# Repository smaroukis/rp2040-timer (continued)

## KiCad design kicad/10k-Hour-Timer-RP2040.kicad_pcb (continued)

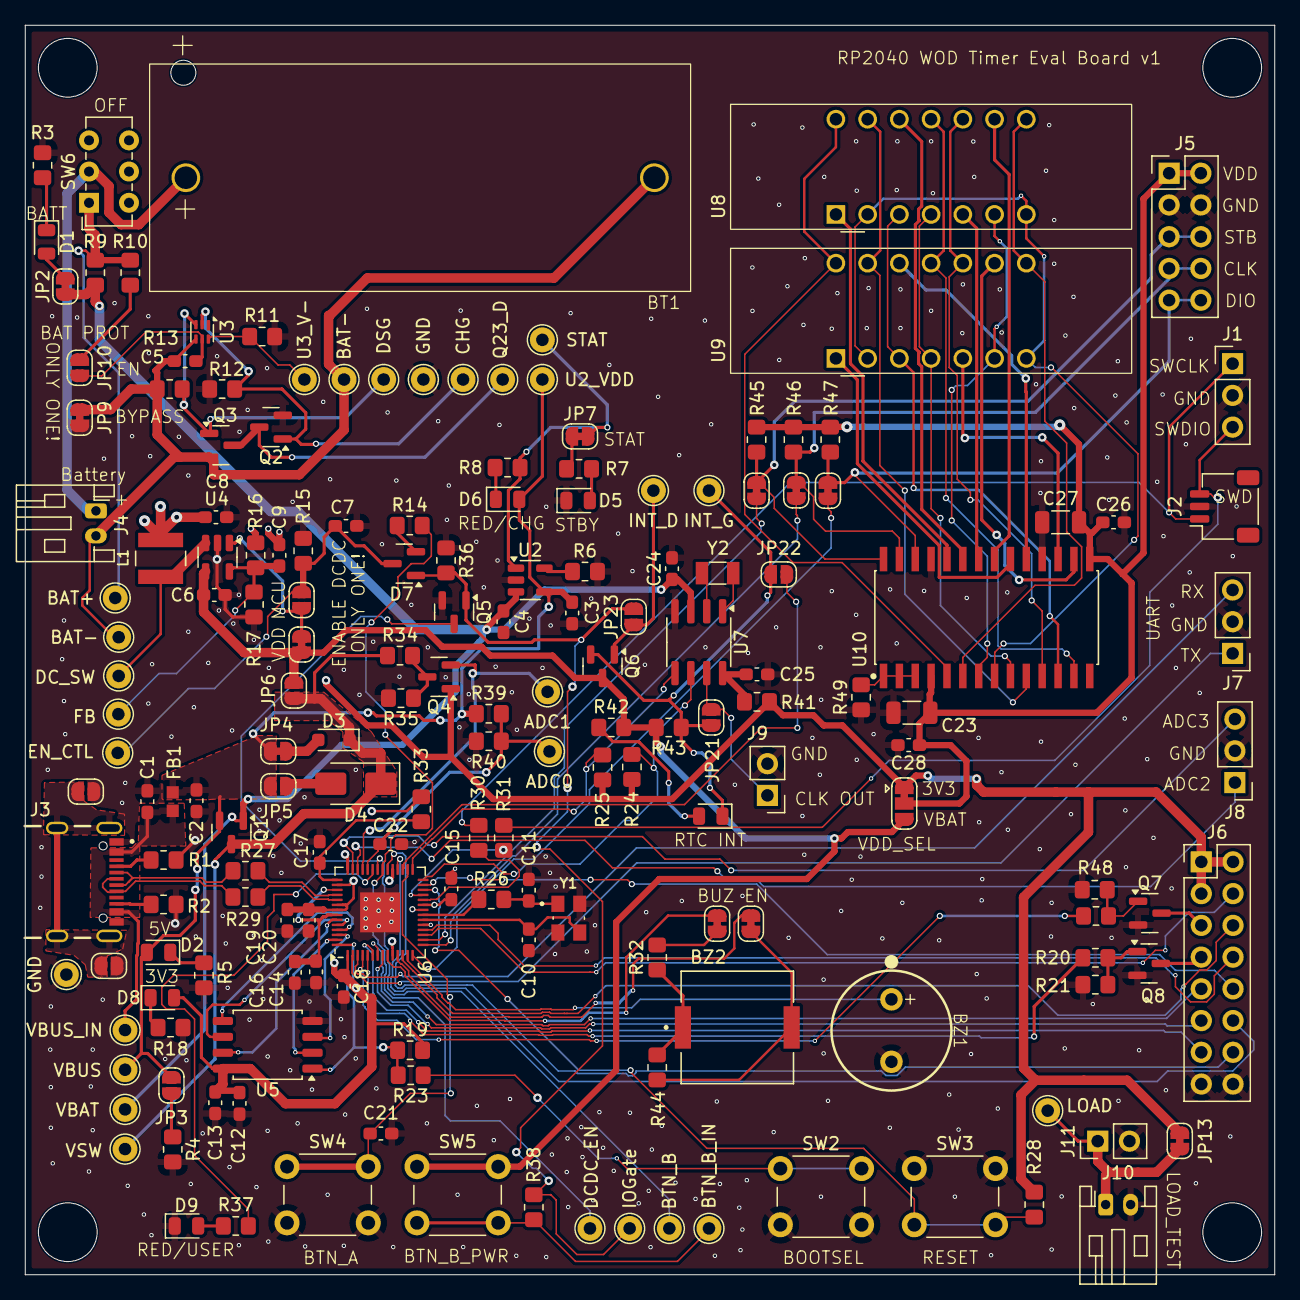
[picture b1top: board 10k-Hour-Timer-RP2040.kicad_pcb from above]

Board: 4 copper layers, 100.0 x 100.0 mm, 180 parts (0 on the bottom side), 128 nets.

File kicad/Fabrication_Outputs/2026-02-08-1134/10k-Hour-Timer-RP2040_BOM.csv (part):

"Subsystem","Reference","Lab_In_Stock","Value","DNP","Exclude from BOM","Exclude from Board","Footprint","Description","Manufacturer","MPN","Supplier 1","Supplier 1 URL","Supplier 1 SKU","Package","Supplier 2 URL","Supplier 2","Supplier 2 SKU"
"","BOM1","","JST PH 2.0mm Connector Kit","DNP","Excluded from BOM","Excluded from board","","For Board Auxiliary order items - connectors, batteries, etc","","","Digikey","https://www.digikey.jp/en/products/detail/adafruit-industrie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","","","","",""
"","BOM2","","Crimp Pliers for JST-PH connectors","DNP","Excluded from BOM","Excluded from board","","Micro terminal crimper down to 1.0mm barrel width. Works well for JST-PH - use the 1.4mm or 1.6mm barrel size.","Engineer","PA-09","Amazon","https://www.amazon.co.jp/-/en/Engineer-Precision-Crimping-Te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","","","","",""
"","BOM3","","Coin Vibration Motor 3V","DNP","Excluded from BOM","Excluded from board","","9000rpm Flat Vibration Motor 3V Vibration Motors ROHS 6mm","Leader","LCM0720A3134F","LCSC","https://lcsc.com/product-detail/Vibration-Motors_LEADER-LCM0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","C2895081","","","",""
"05-MCU-XTAL-FLASH","SW1","Y","B3U-1100PM","DNP","Excluded from BOM","Excluded from board","Button_Switch_SMD:SW_SPST_B3U-1100P","SWITCH TACTILE SPST-NO 0.05A 12V","omron","B3U-1100PM","Digikey","https://www.digikey.jp/en/products/detail/omron-electronics-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","","SMD 4mmx2.5mm","","",""
"04-Batt-Prot","SW6","THS","SW_SPDT","DNP","","","Button_Switch_THT:SW_E-Switch_EG1271_SPDT","Switch, single pole double throw","E-Switch","EG1271","Digikey","https://www.digikey.com/en/products/detail/e-switch/EG1271/251335","","","","",""
"05-MCU-XTAL-FLASH","SW2","Y","BOOTSEL","DNP","","","Button_Switch_THT:SW_PUSH_6mm","Push button switch, generic, two pins","(Generic)/TE","(Generic)/1825910-6","(Generic)/Digikey","https://www.digikey.jp/en/products/detail/te-connectivity-al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","","","","",""
"05-MCU-XTAL-FLASH","SW3","Y","RESET","DNP","","","Button_Switch_THT:SW_PUSH_6mm","Push button switch, generic, two pins","(Generic)/TE","(Generic)/1825910-6","(Generic)/Digikey","https://www.digikey.jp/en/products/detail/te-connectivity-al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","","","","",""
"06-MCU-IO","SW4","Y","USER_A","DNP","","","Button_Switch_THT:SW_PUSH_6mm","Push button switch, generic, two pins","(Generic)/TE","(Generic)/1825910-6","(Generic)/Digikey","https://www.digikey.jp/en/products/detail/te-connectivity-al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","","PB_6x6","","",""
"06-MCU-IO","SW5","Y","USER_B_PWR","DNP","","","Button_Switch_THT:SW_PUSH_6mm","Push button switch, generic, two pins","(Generic)/TE","(Generic)/1825910-6","(Generic)/Digikey","https://www.digikey.jp/en/products/detail/te-connectivity-al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","","PB_6x6","","",""
"01A-USB","C1","Y","10n","","","","Capacitor_SMD:C_0603_1608Metric_Pad1.08x0.95mm_HandSolder","Unpolarized capacitor","(Generic)","(Generic)","(Generic)","","","0603","","",""
"01A-USB,05-MCU-XTAL-FLASH,06-MCU-IO,07-RTC,08-LED","C2,C13,C15,C16,C18,C19,C21,C22,C24,C26,C28","Y","100n","","","","Capacitor_SMD:C_0603_1608Metric_Pad1.08x0.95mm_HandSolder","Unpolarized capacitor","(Generic)","(Generic)","(Generic)","","","0603","","",""
"02-DCDC,03-Charger,07-RTC","C3,C4,C6,C25","Y","4.7u","","","","Capacitor_SMD:C_0603_1608Metric_Pad1.08x0.95mm_HandSolder","Unpolarized capacitor","(Generic)","(Generic)","(Generic)","https://jlcpcb.com/partdetail/20375-CL10A475KO8NNNC/C19666","C19666","0603","","",""
"04-Batt-Prot","C5","Y","0.1u","","","","Capacitor_SMD:C_0603_1608Metric_Pad1.08x0.95mm_HandSolder","Unpolarized capacitor","(Generic)","(Generic)","(Generic)","","","0603","","",""
"02-DCDC","C7","Y","470n","","","","Capacitor_SMD:C_0603_1608Metric_Pad1.08x0.95mm_HandSolder","","(Generic)","(Generic)","(Generic)","","","0603","","",""
"02-DCDC","C8","","22u","","","","Capacitor_SMD:C_0603_1608Metric_Pad1.08x0.95mm_HandSolder","6.3V 22uF X5R ±20% 0603 Multilayer Ceramic Capacitors MLCC - SMD/SMT ROHS","Samsung Electro-Mechanics","CL10A226MQ8NRNC","LCSC","https://jlcpcb.com/partdetail/60514-CL10A226MQ8NRNC/C59461","C59461","0603","","",""
"02-DCDC","C9","Y","6.8p","","","","Capacitor_SMD:C_0603_1608Metric_Pad1.08x0.95mm_HandSolder","","(Generic)","(Generic)","(Generic)","","","0603","","",""
"05-MCU-XTAL-FLASH","C10,C11","Y","15p","","","","Capacitor_SMD:C_0603_1608Metric_Pad1.08x0.95mm_HandSolder","Unpolarized capacitor","(Generic)","(Generic)","(Generic)","","","0603","","",""
"05-MCU-XTAL-FLASH","C12","Y","2.2u","","","","Capacitor_SMD:C_0603_1608Metric_Pad1.08x0.95mm_HandSolder","Unpolarized capacitor","(Generic)","(Generic)","(Generic)","","","0603","","",""
"05-MCU-XTAL-FLASH","C14,C17,C20","Y","1u","","","","Capacitor_SMD:C_0603_1608Metric_Pad1.08x0.95mm_HandSolder","Unpolarized capacitor","(Generic)","(Generic)","(Generic)","","","0603","","",""
"08-LED","C23,C27","","100u","","","","Capacitor_SMD:C_1206_3216Metric","Unpolarized capacitor","Samsung Electro-Mechanics","CL31A107MQHNNNE","LCSC","https://lcsc.com/product-detail/Multilayer-Ceramic-Capacitor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","C15008","1206","","",""
"02-DCDC,04-Batt-Prot","J4,J10","Y","S2B-PH-K-S_LF__SN_","DNP","","","Connector_JST:JST_PH_S2B-PH-K_1x02_P2.00mm_Horizontal","CONN HEADER R/A 2POS 2MM","JST","S2B-PH-K-S","Digikey","https://www.digikey.jp/en/products/detail/jst-sales-america-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","","NON STANDARD-2 J.S.T.","","",""
"07-RTC","J9,J11","Y","Conn_01x02_Pin","DNP","","","Connector_PinHeader_2.54mm:PinHeader_1x02_P2.54mm_Vertical","Generic connector, single row, 01x02, script generated","","","","","","","","",""
"05-MCU-XTAL-FLASH,06-MCU-IO","J1,J7,J8","Y","Conn_01x03_Pin","DNP","","","Connector_PinHeader_2.54mm:PinHeader_1x03_P2.54mm_Vertical","Generic connector, single row, 01x03, script generated","(Embedded)","(Embedded)","(Embedded)","","","","","",""
"06-MCU-IO","J5","Y","Conn_02x05_Counter_Clockwise","DNP","","","Connector_PinHeader_2.54mm:PinHeader_2x05_P2.54mm_Vertical","Generic connector, double row, 02x05, odd/even pin numbering scheme (row 1 odd numbers, row 2 even numbers), script generated (kicad-library-utils/schlib/autogen/connector/)","","","","","","","","",""
"","J6","Y","Conn_02x08_Counter_Clockwise","DNP","","","Connector_PinHeader_2.54mm:PinHeader_2x08_P2.54mm_Vertical","Generic connector, double row, 02x08, odd/even pin numbering scheme (row 1 odd numbers, row 2 even numbers), script generated (kicad-library-utils/schlib/autogen/connector/)","","","","","","","","",""
"07-RTC","Y2","","ABS07AIG-32.768KHZ-7-T","","","","Crystal:Crystal_SMD_3215-2Pin_3.2x1.5mm","32.768 kHz ±20ppm 水晶振動子 7pF 80 kOhms 2-SMD、リードなし","Abracon LLC","ABS07AIG-32.768KHZ-7-T","Digikey","https://www.digikey.jp/ja/products/detail/abracon-llc/ABS07A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","535-13350-1-ND","2-SMD（3.2x1.5）","","",""
"01A-Power-Mux","D4","","SS14","","","","Diode_SMD:D_SMA","40V 1A Schottky Diode, SMA","onsemi","SS14 (Generic)","Generic","https://lcsc.com/product-detail/Schottky-Diodes_onsemi-SS14_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","C83852","SMA(DO-214AC)","","",""
"01A-Power-Mux","D3","","SOD-323","","","","Diode_SMD:D_SOD-323_HandSoldering","10V 460mV@2A 2A SOD-323 Schottky Diodes ROHS","Nexperia","PMEG1020EA,115","LCSC","https://lcsc.com/product-detail/Schottky-Diodes_Nexperia-PME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","C426863","SOD-323","","",""
"01A-Power-Mux,06-MCU-IO","JP2,JP4,JP7,JP9,JP11,JP13,JP16,JP17,JP18,JP19,JP20","","SolderJumper_2_Bridged","","Excluded from BOM","","Jumper:SolderJumper-2_P1.3mm_Bridged_RoundedPad1.0x1.5mm","Solder Jumper, 2-pole, closed/bridged","","(Embedded)","","","","","","",""
"01A-Power-Mux,01A-USB,07-RTC","JP1,JP3,JP5,JP6,JP10,JP12,JP21,JP22,JP23,JP24","","SolderJumper_2_Open","","Excluded from BOM","","Jumper:SolderJumper-2_P1.3mm_Open_RoundedPad1.0x1.5mm","Solder Jumper, 2-pole, open","","(Embedded)","","","","","","",""
"","JP8","","SolderJumper_3_Bridged12","","Excluded from BOM","","Jumper:SolderJumper-3_P1.3mm_Bridged12_RoundedPad1.0x1.5mm","3-pole Solder Jumper, pins 1+2 closed/bridged","","","","","","","","",""
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
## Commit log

2025-07-06 Initial commit - 10k-Hour-Timer-RP2040 project
    - KiCad schematic and PCB design files
    - Project structure with datasheets and firmware directories
    - README with project overview
2025-07-06 3d model imports
2025-07-07 added charger and power mux
2025-07-08 battery charger and protection
2025-07-09 battery protection and connector
2025-07-09 dc dc start
2025-07-10 test push
2025-07-10 test
2025-07-10 working on dcdc
2025-07-10 dcdc enable and swd
2025-07-13 rp2040 chip start
2025-07-13 mcu periphs
2025-07-14 clock input pins for internal rtc
2025-07-14 added 32.768 oscillator
2025-07-15 low speed xtal added
2025-07-15 external RTC start
2025-07-15 rtc research
2025-07-16 rtc hardware
2025-07-16 rtc additions
2025-07-17 buzzer
2025-07-18 DR ✅ SYS-01-Power-Mux
2025-07-18 DR SYS-02-DCDC ✅
2025-07-18 led indicator silks
2025-07-19 DR SYS-03 Charger ✅
2025-07-19 charger pcb update
2025-07-20 DR SYS-04-Battery Protect ✅
2025-07-20 DR SYS-05-MCU XTAL
2025-07-21 DR SYS-06-MCU-IO ✅
2025-07-22 buzzer edits
2025-07-26 rtc new sheet, pullups
2025-07-27 pre ERC
2025-07-27 ERC done
2025-07-27 floorplanning
2025-07-28 buzzer fp, power mux layout
2025-07-29 layout battery protection
2025-07-29 layout floorplanning
2025-07-30 layout rtc
2025-07-31 resize
2025-07-31 floorplanning batt prot
2025-08-02 layout - 7seg display
2025-08-02 layout - footprints update - may have corrupted kicad_sch project lib
2025-08-02 floorplanning - fixed 7seg symbol issue
2025-08-04 start routing diff pairs
2025-08-04 changed usb port, prepare first bom export
2025-08-05 routing - power
2025-08-11 routing - 3v3 net
2025-08-13 routing - adc
2025-08-16 routing - GPIOs
2025-08-17 DRC to zero errors - still need to check FPs
2025-08-17 prep for FP changes
2025-08-17 updated FPs, ready for final DR before fab
2025-08-31 unknown changes
2026-02-08 production files for PCBWay initial - BOM manually edited for PCBA
2026-02-12 fabrication files, after edits for pcbway 2-12
2026-03-22 prep for release v1 as built from PCBWay
